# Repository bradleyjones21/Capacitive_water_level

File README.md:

# Capacitive_water_level
A custom designed capacitive water level sensor in KiCAD.
Tested and works well with a linear voltage response for the whole length of the board.

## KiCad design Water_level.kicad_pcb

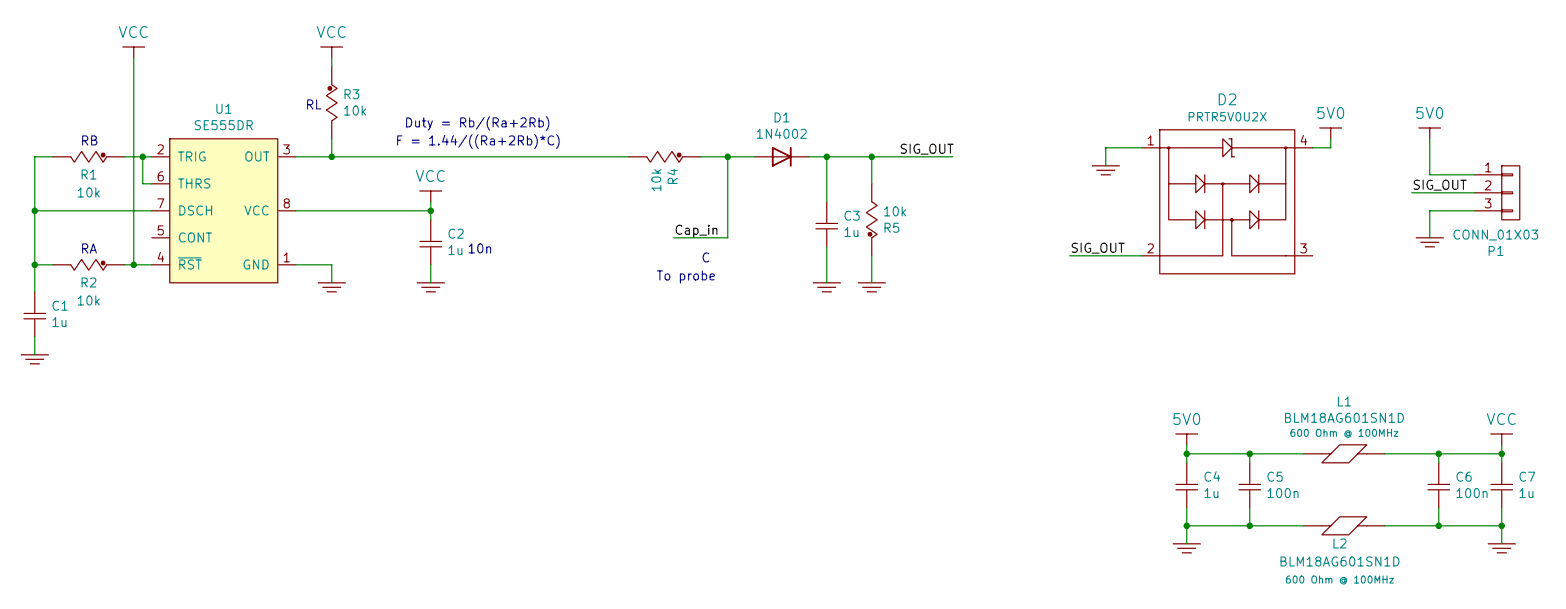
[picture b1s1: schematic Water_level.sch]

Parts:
C1, C2, C3, C4, C7: 1u; C_0603_1608Metric_Pad1.05x0.95mm_HandSolder; VOLTAGE 35V; TOLERANCE 10%
C5, C6: 100n; C_0603_1608Metric_Pad1.05x0.95mm_HandSolder; VOLTAGE 35V; TOLERANCE 10%
D1: 1N4002; D_0603_1608Metric_Pad1.05x0.95mm_HandSolder
D2: PRTR5V0U2X; SOT-143
L1, L2: BLM18AG601SN1D; C_0603_1608Metric_Pad1.05x0.95mm_HandSolder
P1: CONN_01X03; PinHeader_1x03_P2.54mm_Vertical
R1, R2, R3: 10k; eR_0603; TOLERANCE 1%
R4, R5: 10k; R_0603_1608Metric_Pad1.05x0.95mm_HandSolder; TOLERANCE 1%
U1: SE555DR; SOIC-8_3.9x4.9mm_P1.27mm

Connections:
5V0: C4.1, C5.1, D2.4, L1.1, P1.1
/Cap_in: D1.2 (A), R4.1
/SIG_OUT: C3.1, D1.1 (K), D2.2, P1.2, R5.2
GND: C1.2, C2.2, C3.2, C4.2, C5.2, C6.2, C7.2, D2.1, L2.1, L2.2, P1.3, R5.1, U1.1 (GND)
unnamed: C1.1, R1.2, R2.2, U1.7 (DSCH)
unnamed: R1.1, U1.2 (TRIG), U1.6 (THRS)
unnamed: R3.2, R4.2, U1.3 (OUT)
VCC: C2.1, C6.1, C7.1, L1.2, R2.1, R3.1, U1.4 (~RST), U1.8 (VCC)

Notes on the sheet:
F = 1.44/((Ra+2Rb)*C)
Duty = Rb/(Ra+2Rb)
To probe
10n

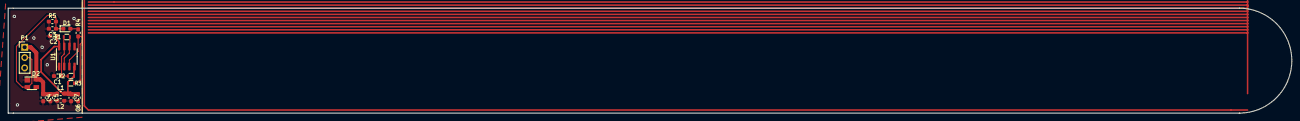
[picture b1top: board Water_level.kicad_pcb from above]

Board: 2 copper layers, 317.0 x 25.9 mm, 18 parts (0 on the bottom side), 8 nets.

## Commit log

2022-03-11 init transfer
